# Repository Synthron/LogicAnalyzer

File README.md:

# LogicAnalyzer
Customized Hardware from https://github.com/gusmanb/logicanalyzer

## Changes
- 0603 parts instead of 0402
- changed pin header pinout for more logical routing
- omission of one pin header for daisy-chaining
- length-matching for all traces

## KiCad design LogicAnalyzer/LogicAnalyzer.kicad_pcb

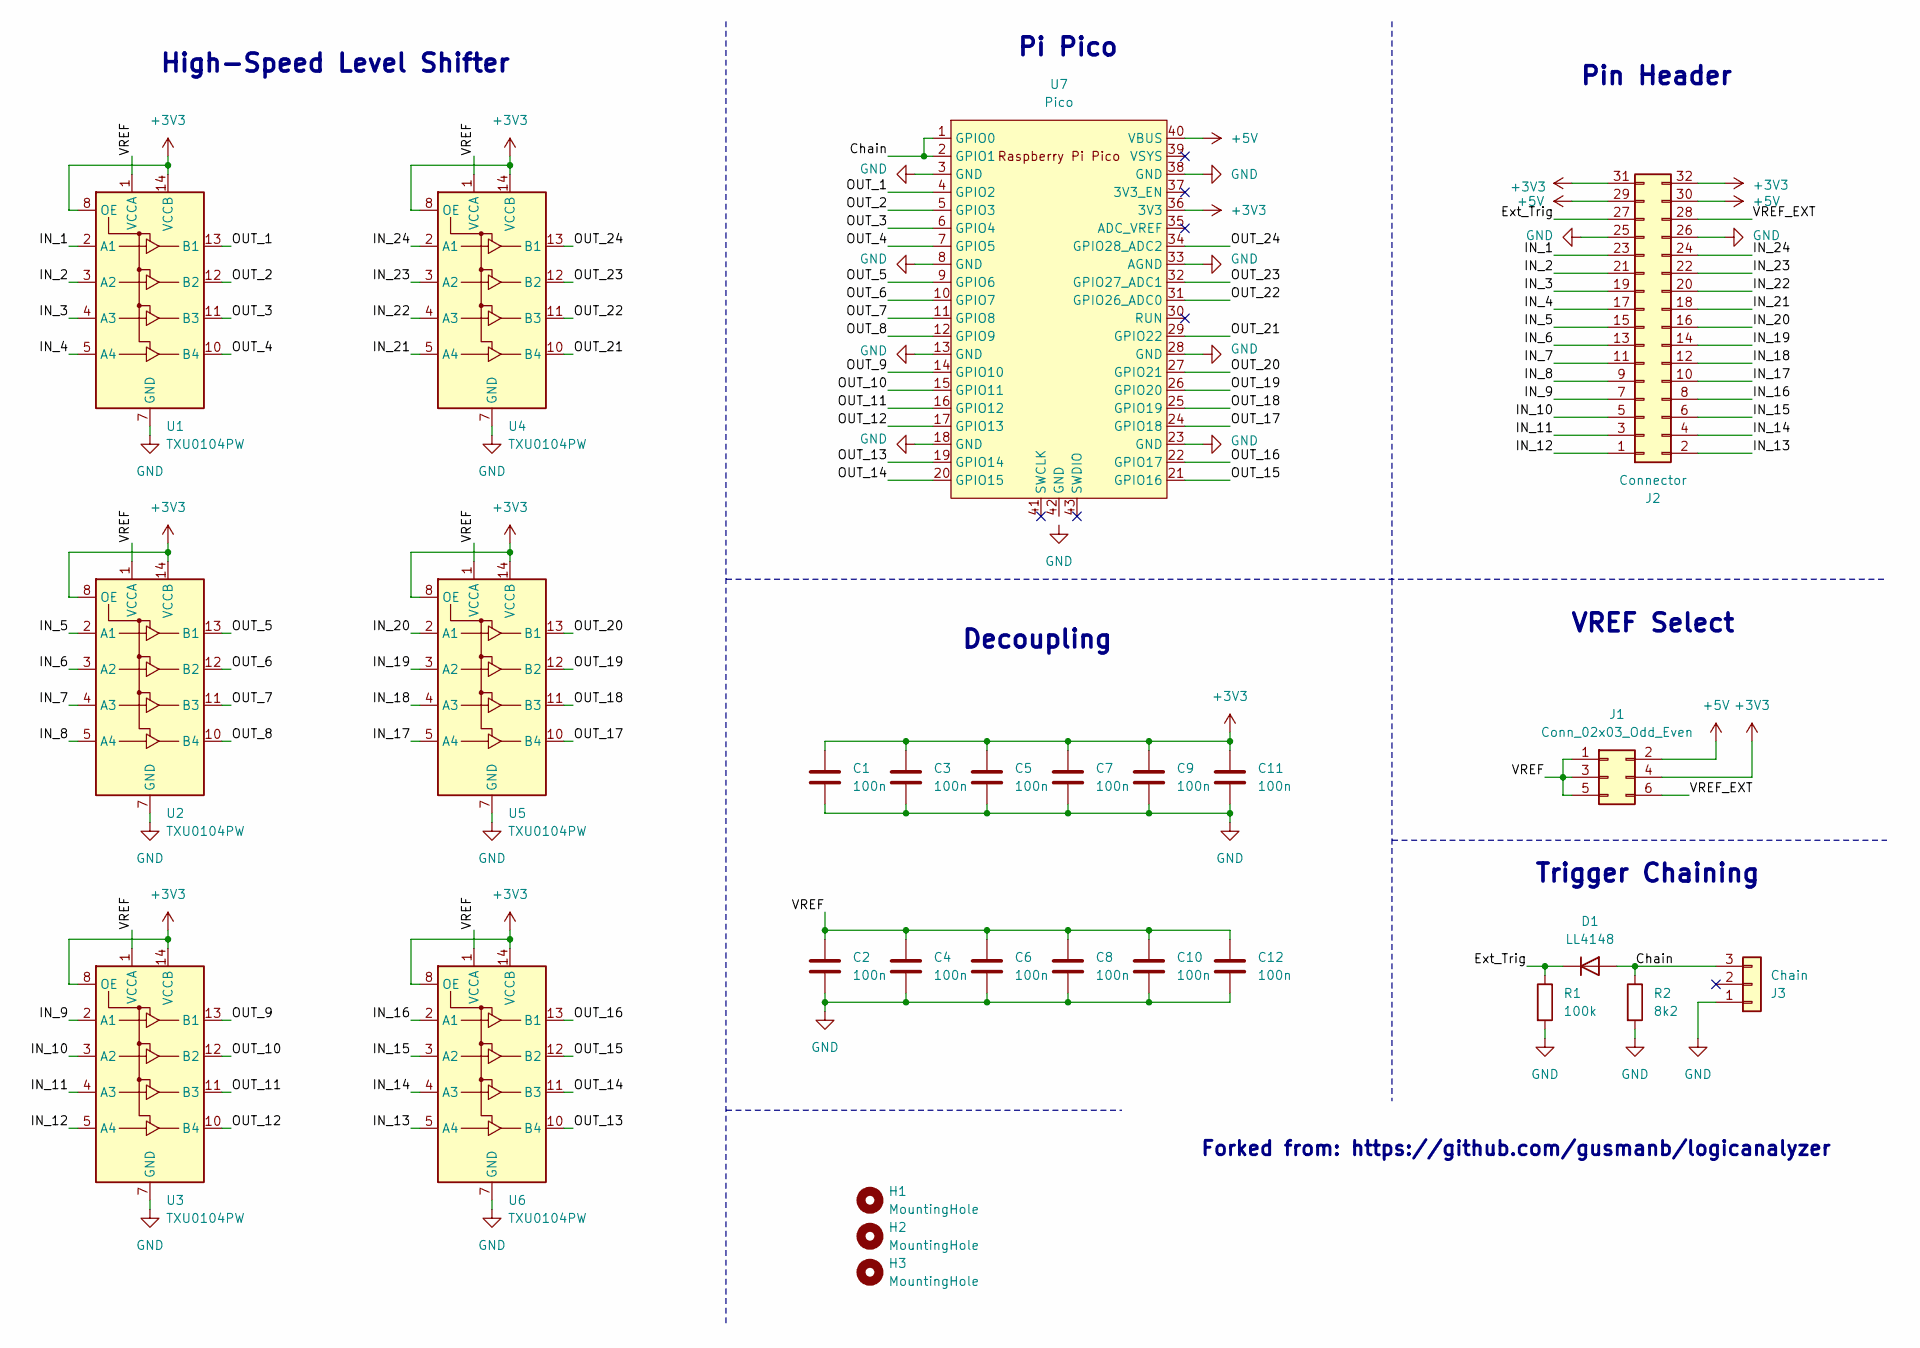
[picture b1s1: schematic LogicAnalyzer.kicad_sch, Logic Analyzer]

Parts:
C1, C2, C3, C4, C5, C6, C7, C8, C9, C10, C11, C12: 100n; C_0603_1608Metric
D1: LL4148; D_MiniMELF
H1, H2, H3: MountingHole; MountingHole_3.2mm_M3_DIN965
J1: Conn_02x03_Odd_Even; PinHeader_2x03_P2.54mm_Vertical
J2: Connector; PinHeader_2x16_P2.54mm_Horizontal
J3: Chain; PinHeader_1x03_P2.54mm_Horizontal
R1: 100k; R_0603_1608Metric
R2: 8k2; R_0603_1608Metric
U1, U2, U3, U4, U5, U6: TXU0104PW; TSSOP-14_4.4x5mm_P0.65mm
U7: Pico; RPi_Pico_SMD_TH

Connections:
+3V3: C1.1, C3.1, C5.1, C7.1, C9.1, C11.1, J1.4, J2.31, J2.32, U1.8 (OE), U1.14 (VCCB), U2.8 (OE), U2.14 (VCCB), U3.8 (OE), U3.14 (VCCB), U4.8 (OE), U4.14 (VCCB), U5.8 (OE), U5.14 (VCCB), U6.8 (OE), U6.14 (VCCB), U7.36 (3V3)
+5V: J1.2, J2.29, J2.30, U7.40 (VBUS)
/Chain: D1.2 (A), J3.3, R2.1, U7.1 (GPIO0), U7.2 (GPIO1)
/Ext_Trig: D1.1 (K), J2.27, R1.1
/IN_1: J2.23, U1.2 (A1)
/IN_2: J2.21, U1.3 (A2)
/IN_3: J2.19, U1.4 (A3)
/IN_4: J2.17, U1.5 (A4)
/IN_5: J2.15, U2.2 (A1)
/IN_6: J2.13, U2.3 (A2)
/IN_7: J2.11, U2.4 (A3)
/IN_8: J2.9, U2.5 (A4)
/IN_9: J2.7, U3.2 (A1)
/IN_10: J2.5, U3.3 (A2)
/IN_11: J2.3, U3.4 (A3)
/IN_12: J2.1, U3.5 (A4)
/IN_13: J2.2, U6.5 (A4)
/IN_14: J2.4, U6.4 (A3)
/IN_15: J2.6, U6.3 (A2)
/IN_16: J2.8, U6.2 (A1)
/IN_17: J2.10, U5.5 (A4)
/IN_18: J2.12, U5.4 (A3)
/IN_19: J2.14, U5.3 (A2)
/IN_20: J2.16, U5.2 (A1)
/IN_21: J2.18, U4.5 (A4)
/IN_22: J2.20, U4.4 (A3)
/IN_23: J2.22, U4.3 (A2)
/IN_24: J2.24, U4.2 (A1)
/OUT_1: U1.13 (B1), U7.4 (GPIO2)
/OUT_2: U1.12 (B2), U7.5 (GPIO3)
/OUT_3: U1.11 (B3), U7.6 (GPIO4)
/OUT_4: U1.10 (B4), U7.7 (GPIO5)
/OUT_5: U2.13 (B1), U7.9 (GPIO6)
/OUT_6: U2.12 (B2), U7.10 (GPIO7)
/OUT_7: U2.11 (B3), U7.11 (GPIO8)
/OUT_8: U2.10 (B4), U7.12 (GPIO9)
/OUT_9: U3.13 (B1), U7.14 (GPIO10)
/OUT_10: U3.12 (B2), U7.15 (GPIO11)
/OUT_11: U3.11 (B3), U7.16 (GPIO12)
/OUT_12: U3.10 (B4), U7.17 (GPIO13)
/OUT_13: U6.10 (B4), U7.19 (GPIO14)
/OUT_14: U6.11 (B3), U7.20 (GPIO15)
/OUT_15: U6.12 (B2), U7.21 (GPIO16)
/OUT_16: U6.13 (B1), U7.22 (GPIO17)
/OUT_17: U5.10 (B4), U7.24 (GPIO18)
/OUT_18: U5.11 (B3), U7.25 (GPIO19)
/OUT_19: U5.12 (B2), U7.26 (GPIO20)
/OUT_20: U5.13 (B1), U7.27 (GPIO21)
/OUT_21: U4.10 (B4), U7.29 (GPIO22)
/OUT_22: U4.11 (B3), U7.31 (GPIO26_ADC0)
/OUT_23: U4.12 (B2), U7.32 (GPIO27_ADC1)
/OUT_24: U4.13 (B1), U7.34 (GPIO28_ADC2)
/VREF: C2.1, C4.1, C6.1, C8.1, C10.1, C12.1, J1.1, J1.3, J1.5, U1.1 (VCCA), U2.1 (VCCA), U3.1 (VCCA), U4.1 (VCCA), U5.1 (VCCA), U6.1 (VCCA)
/VREF_EXT: J1.6, J2.28
GND: C1.2, C2.2, C3.2, C4.2, C5.2, C6.2, C7.2, C8.2, C9.2, C10.2, C11.2, C12.2, J2.25, J2.26, J3.1, R1.2, R2.2, U1.7 (GND), U2.7 (GND), U3.7 (GND), U4.7 (GND), U5.7 (GND), U6.7 (GND), U7.3 (GND), U7.8 (GND), U7.13 (GND), U7.18 (GND), U7.23 (GND), U7.28 (GND), U7.33 (AGND), U7.38 (GND)

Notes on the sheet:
VREF Select
Pi Pico
Decoupling
Forked from: https://github.com/gusmanb/logicanalyzer
Pin Header
High-Speed Level Shifter
Trigger Chaining

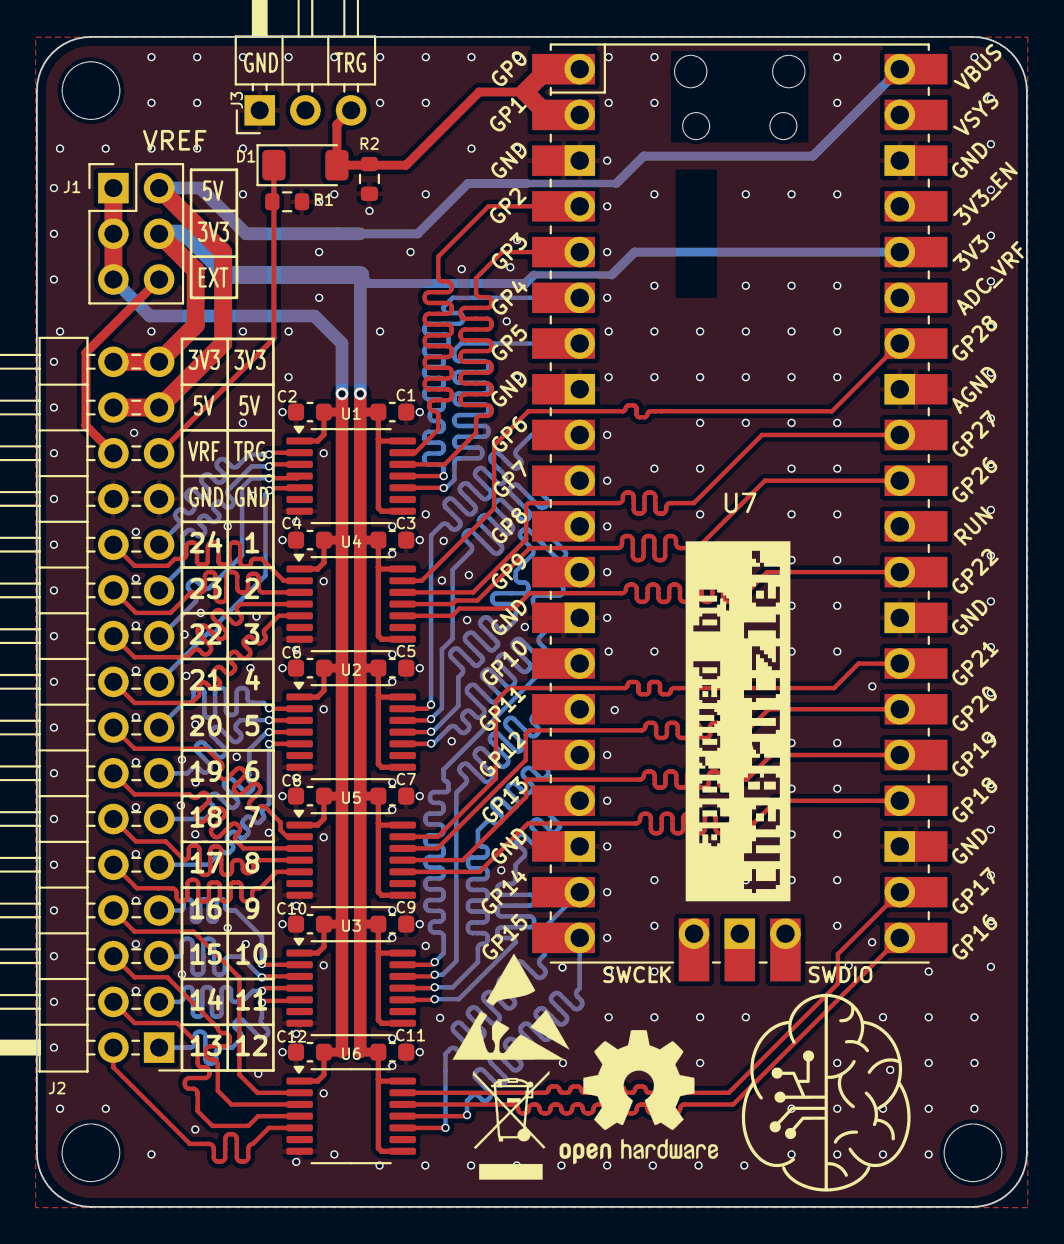
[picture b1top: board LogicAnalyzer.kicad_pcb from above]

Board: 4 copper layers, 55.0 x 65.0 mm, 28 parts (0 on the bottom side), 55 nets.

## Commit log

2025-04-21 readme update
2025-04-22 PCB update
2025-04-22 Schematic Update Level Shifter Type
2025-04-23 added via stitching
2025-04-23 DRC Check
2025-04-25 Brutzler Review
2025-04-26 add gerbers
2025-05-19 add 6502 decoder
2025-05-20 update with comments
2025-05-25 working opcode disassembly
2025-05-25 working cycle decoding
